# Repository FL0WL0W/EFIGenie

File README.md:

# EFIGenie

An open source engine management. It uses a taskmanager and is coded in a
operation oriented architecture.

The target microcontroller at the moment are the cheap but powerful STM32 line of processors
but any microcontroller can be ported by creating just 4 services,
AnalogService, DigitalService, PwmService, TimerService that can be found in the https://github.com/FL0WL0W/EmbeddedIOServices 
repository. A large benefit to this architecture is that new sensors/abilities/features/etc. 
can be added very easily and can be chosen between the old and new through the configs. 
which means decoders can be changed, sensors added or removed, features added or removed. 
all without having to recompile. There are also some wrapper classes where things like 
two step rev limiters can be implemented or tri-step or even quad-step. still have a list of
things to complete but i am at a state where i am testing the ecu. At this point it has run an engine https://www.youtube.com/watch?v=jJOaTFBkKEE

## Features
* Customizable(size, limits, and axis) 3D Fuel and Ignition Maps (Speed Density, Alpha N)
* Customizable formulas for all engine parameters
* Cusotmizable inputs and outputs
* Unlimited cylinder sequential injection and ignition (Depends on hardware)
  * Stm32Devboard - 8 cylinder sequential fuel and ignition (10, 12, 14, 16 wasted spark/banked injection)
* Flexible Crank Cam Decoder
  * GM 24x (Cam + Crank, Crank Only, or Cam only)
  * Universal 1X decoder
  * Configurable Missing Tooth Decoder
  * --More to come
* Firmware features
  * Unit Tests to ensure everything works
  * Operation Architecture
  * Easily add new sensors

## Diagnostic data handlers

`CommunicationHandler_OBD2PIDRequester` and `CommunicationHandler_OBD2PIDResponder`
use Service `0x01`/`0x41` and 8-bit PIDs. UDS Service `0x22`/`0x62` uses the separate
`CommunicationHandler_UDSDIDRequester` and `CommunicationHandler_UDSDIDResponder`
with 16-bit DIDs. Move existing 16-bit `RegisterPID`/`RequestPID` calls to
`RegisterDID`/`RequestDID`; the service is no longer selected by identifier size.

To expose a PID responder through a DID range:

```cpp
EFIGenie::CommunicationHandler_OBD2PIDResponder pids(communicationService);
EFIGenie::CommunicationHandler_UDSDIDResponder dids(communicationService);
pids.RegisterPID(0x0c, rpmOperation);
dids.RegisterOBD2PIDMirror(0xf4, &pids);
```

A request `22 F4 0C` calls the PID responder locally with `01 0C`, captures its
`41 0C <payload>` response, and returns `62 F4 0C <payload>`. No OBD request is
sent on the bus. The high byte is configurable; supported-PID bitmap requests
are mirrored too, and later PID registrations/unregistrations are reflected
immediately. Explicit `RegisterDID` entries override mirrored entries. Use
`UnregisterOBD2PIDMirror(highByte)` to remove a mirror. Operations and mirrored
responders are borrowed and must outlive their registrations.

The DID responder accepts framed requests containing one or more DIDs, returning
one combined positive response or a negative response if any requested value is
unavailable. Malformed frames return `7F 22 13`; unavailable values return
`7F 22 31`. The DID requester requests and parses one DID per transaction because
multi-DID response payload lengths require application-specific definitions.

## Building
After trying with a few different toolchains the tool chain that seemed to work the best is GCC/G++9.

* Ubuntu 20.04
* GCC/G++9
* CMake

VSCode Extensions:
* C/C++
* CMake
* CMake Tools
* Cortex-Debug
* GoogleTest Adapter

```
sudo apt-get install cmake gcc g++ gdb
```

### Building the Tests
Make 

## TODO List
* *Idle Control
* After Start Enrichment (Add Engine Time Since Started, AE can be configured in GUI with that variable available)
* Customizable(size and seperations) FuelTrim Predictive Multi Channel Historic Table
* Fuel Trim (Wideband/Pid and Narrowband | predictive based on TPS or MAP)
* Transmission Control (Paddle shift transmission solenoid)
* Transmission Control (line pressure control)
* Transmission Control (automatic gear shifts)
* OBD2

> *High Priority

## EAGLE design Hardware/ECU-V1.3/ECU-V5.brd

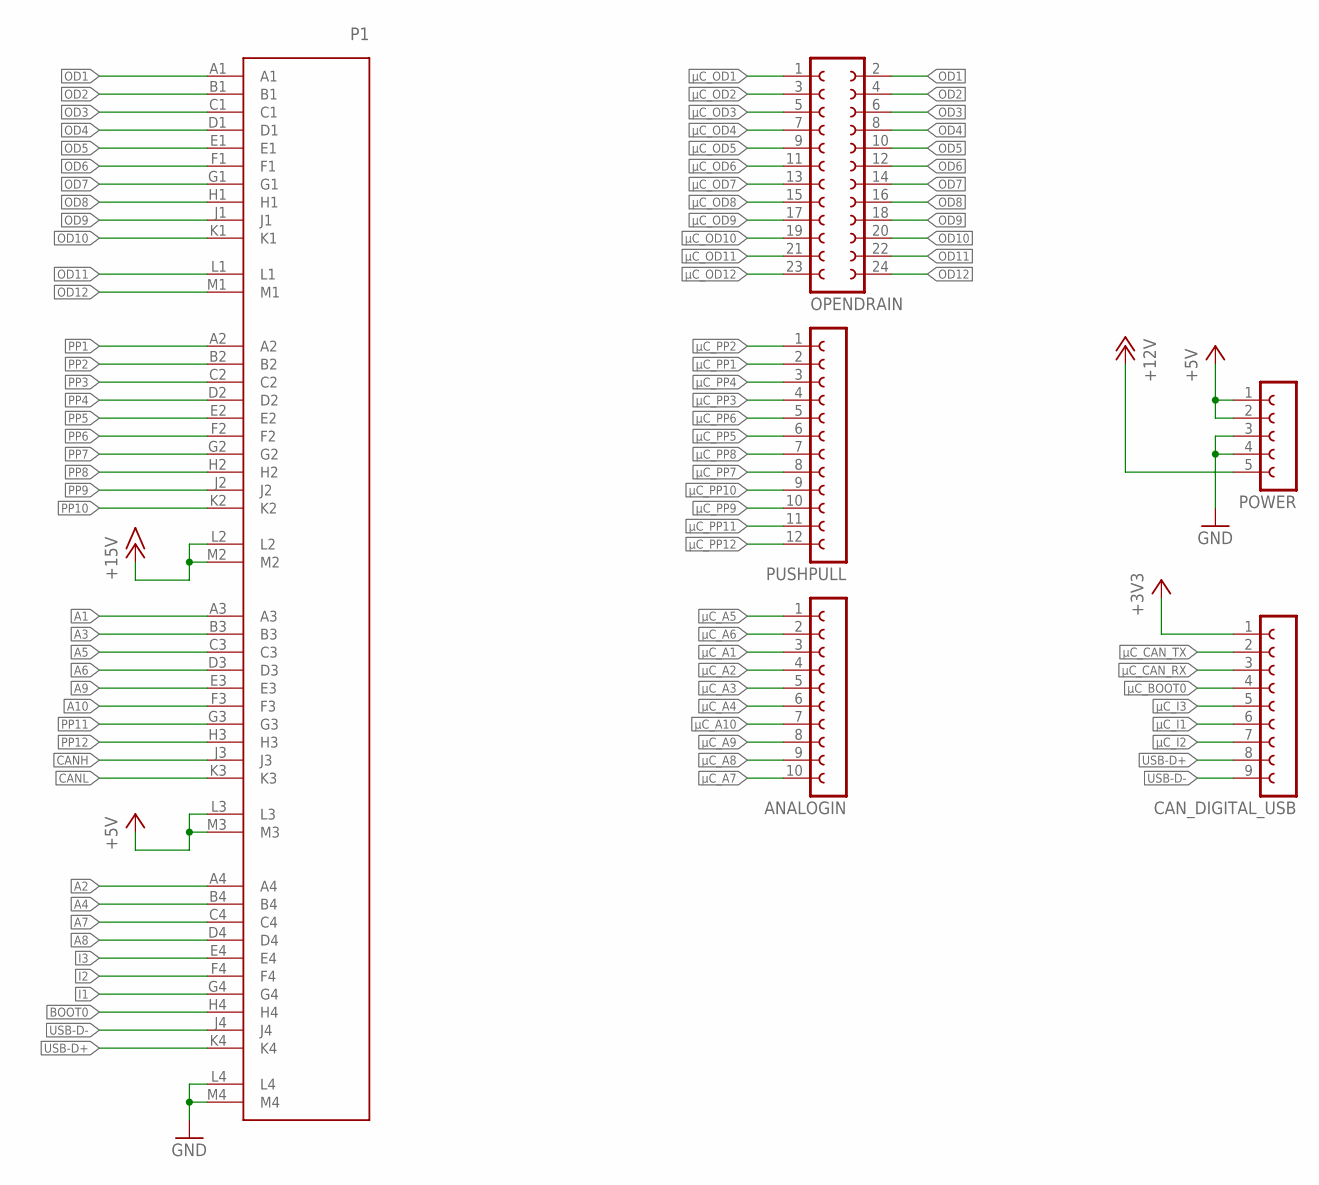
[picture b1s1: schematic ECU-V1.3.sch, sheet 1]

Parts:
ANALOGIN: FE10-1; FE10
CAN_DIGITAL_USB: FE09-1; FE09
OPENDRAIN: FE12-2
P1: ECU-CONNECTOR
POWER: FE05-1
PUSHPULL: FE12-1; FE12

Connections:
+3V3: CAN_DIGITAL_USB.1; also elsewhere on the board
+5V: P1.L3, P1.M3, POWER.1, POWER.2; also elsewhere on the board
+12V: POWER.5; also elsewhere on the board
+15V: P1.L2, P1.M2; also elsewhere on the board
A1: P1.A3; also elsewhere on the board
A2: P1.A4; also elsewhere on the board
A3: P1.B3; also elsewhere on the board
A4: P1.B4; also elsewhere on the board
A5: P1.C3; also elsewhere on the board
A6: P1.D3; also elsewhere on the board
A7: P1.C4; also elsewhere on the board
A8: P1.D4; also elsewhere on the board
A9: P1.E3; also elsewhere on the board
A10: P1.F3; also elsewhere on the board
BOOT0: P1.H4; also elsewhere on the board
CANH: P1.J3; also elsewhere on the board
CANL: P1.K3; also elsewhere on the board
GND: P1.L4, P1.M4, POWER.3, POWER.4; also elsewhere on the board
I1: P1.G4; also elsewhere on the board
I2: P1.F4; also elsewhere on the board
I3: P1.E4; also elsewhere on the board
OD1: OPENDRAIN.2, P1.A1; also elsewhere on the board
OD2: OPENDRAIN.4, P1.B1; also elsewhere on the board
OD3: OPENDRAIN.6, P1.C1; also elsewhere on the board
OD4: OPENDRAIN.8, P1.D1; also elsewhere on the board
OD5: OPENDRAIN.10, P1.E1; also elsewhere on the board
OD6: OPENDRAIN.12, P1.F1; also elsewhere on the board
OD7: OPENDRAIN.14, P1.G1; also elsewhere on the board
OD8: OPENDRAIN.16, P1.H1; also elsewhere on the board
OD9: OPENDRAIN.18, P1.J1; also elsewhere on the board
OD10: OPENDRAIN.20, P1.K1; also elsewhere on the board
OD11: OPENDRAIN.22, P1.L1; also elsewhere on the board
OD12: OPENDRAIN.24, P1.M1; also elsewhere on the board
PP1: P1.A2; also elsewhere on the board
PP2: P1.B2; also elsewhere on the board
PP3: P1.C2; also elsewhere on the board
PP4: P1.D2; also elsewhere on the board
PP5: P1.E2; also elsewhere on the board
PP6: P1.F2; also elsewhere on the board
PP7: P1.G2; also elsewhere on the board
PP8: P1.H2; also elsewhere on the board
PP9: P1.J2; also elsewhere on the board
PP10: P1.K2; also elsewhere on the board
PP11: P1.G3; also elsewhere on the board
PP12: P1.H3; also elsewhere on the board
USB-D+: CAN_DIGITAL_USB.8, P1.K4
USB-D-: CAN_DIGITAL_USB.9, P1.J4
µC_A1: ANALOGIN.3; also elsewhere on the board
µC_A2: ANALOGIN.4; also elsewhere on the board
µC_A3: ANALOGIN.5; also elsewhere on the board
µC_A4: ANALOGIN.6; also elsewhere on the board
µC_A5: ANALOGIN.1; also elsewhere on the board
µC_A6: ANALOGIN.2; also elsewhere on the board
µC_A7: ANALOGIN.10; also elsewhere on the board
µC_A8: ANALOGIN.9; also elsewhere on the board
µC_A9: ANALOGIN.8; also elsewhere on the board
µC_A10: ANALOGIN.7; also elsewhere on the board
µC_BOOT0: CAN_DIGITAL_USB.4; also elsewhere on the board
µC_CAN_RX: CAN_DIGITAL_USB.3; also elsewhere on the board
µC_CAN_TX: CAN_DIGITAL_USB.2; also elsewhere on the board
µC_I1: CAN_DIGITAL_USB.6; also elsewhere on the board
µC_I2: CAN_DIGITAL_USB.7; also elsewhere on the board
µC_I3: CAN_DIGITAL_USB.5; also elsewhere on the board
µC_OD1: OPENDRAIN.1; also elsewhere on the board
µC_OD2: OPENDRAIN.3; also elsewhere on the board
µC_OD3: OPENDRAIN.5; also elsewhere on the board
µC_OD4: OPENDRAIN.7; also elsewhere on the board
µC_OD5: OPENDRAIN.9; also elsewhere on the board
µC_OD6: OPENDRAIN.11; also elsewhere on the board
µC_OD7: OPENDRAIN.13; also elsewhere on the board
µC_OD8: OPENDRAIN.15; also elsewhere on the board
µC_OD9: OPENDRAIN.17; also elsewhere on the board
µC_OD10: OPENDRAIN.19; also elsewhere on the board
µC_OD11: OPENDRAIN.21; also elsewhere on the board
µC_OD12: OPENDRAIN.23; also elsewhere on the board
µC_PP1: PUSHPULL.2; also elsewhere on the board
µC_PP2: PUSHPULL.1; also elsewhere on the board
µC_PP3: PUSHPULL.4; also elsewhere on the board
µC_PP4: PUSHPULL.3; also elsewhere on the board
µC_PP5: PUSHPULL.6; also elsewhere on the board
µC_PP6: PUSHPULL.5; also elsewhere on the board
µC_PP7: PUSHPULL.8; also elsewhere on the board
µC_PP8: PUSHPULL.7; also elsewhere on the board
µC_PP9: PUSHPULL.10; also elsewhere on the board
µC_PP10: PUSHPULL.9; also elsewhere on the board
µC_PP11: PUSHPULL.11; also elsewhere on the board
µC_PP12: PUSHPULL.12; also elsewhere on the board

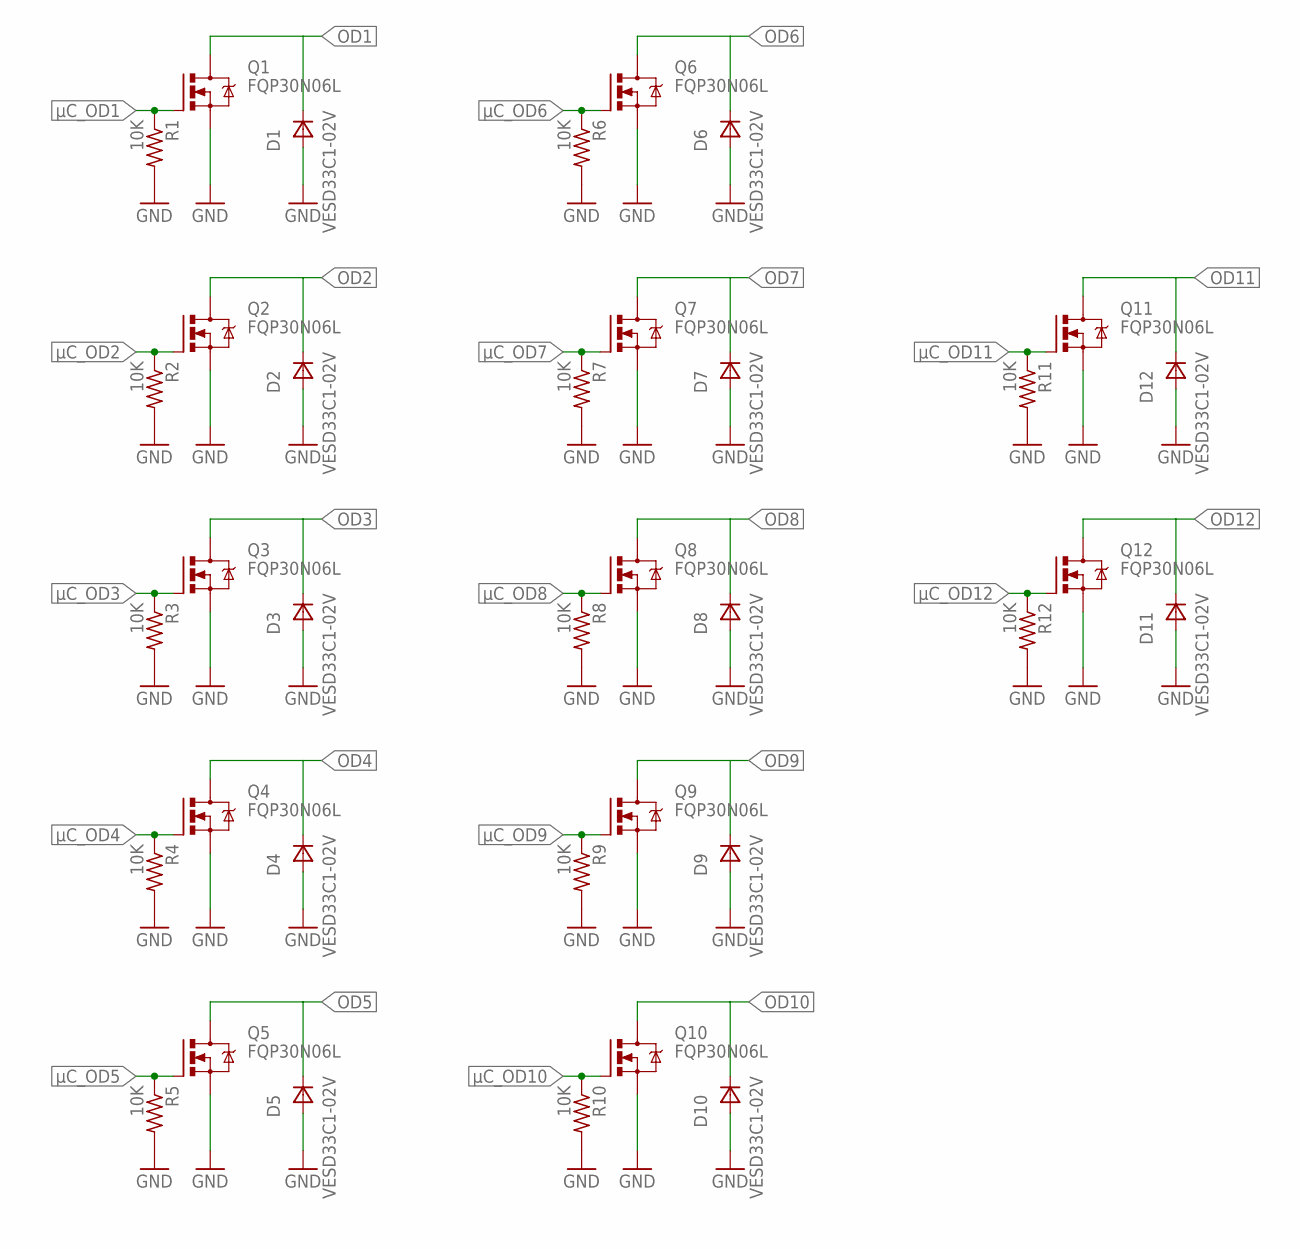
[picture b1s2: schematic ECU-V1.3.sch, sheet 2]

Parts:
D1, D2, D3, D4, D5, D6, D7, D8, D9, D10, D11, D12: VESD33C1-02V; SOD323
Q1, Q2, Q3, Q4, Q5, Q6, Q7, Q8, Q9, Q10, Q11, Q12: FQP30N06L; TO220BV
R1, R2, R3, R4, R5, R6, R7, R8, R9, R10, R11, R12: 10K; R0805

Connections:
GND: D1.2 (A), D2.2 (A), D3.2 (A), D4.2 (A), D5.2 (A), D6.2 (A), D7.2 (A), D8.2 (A), D9.2 (A), D10.2 (A), D11.2 (A), D12.2 (A), Q1.S, Q2.S, Q3.S, Q4.S, Q5.S, Q6.S, Q7.S, Q8.S, Q9.S, Q10.S, Q11.S, Q12.S, R1.2, R2.2, R3.2, R4.2, R5.2, R6.2, R7.2, R8.2, R9.2, R10.2, R11.2, R12.2; also elsewhere on the board
OD1: D1.1 (C), Q1.D; also elsewhere on the board
OD2: D2.1 (C), Q2.D; also elsewhere on the board
OD3: D3.1 (C), Q3.D; also elsewhere on the board
OD4: D4.1 (C), Q4.D; also elsewhere on the board
OD5: D5.1 (C), Q5.D; also elsewhere on the board
OD6: D6.1 (C), Q6.D; also elsewhere on the board
OD7: D7.1 (C), Q7.D; also elsewhere on the board
OD8: D8.1 (C), Q8.D; also elsewhere on the board
OD9: D9.1 (C), Q9.D; also elsewhere on the board
OD10: D10.1 (C), Q10.D; also elsewhere on the board
OD11: D12.1 (C), Q11.D; also elsewhere on the board
OD12: D11.1 (C), Q12.D; also elsewhere on the board
µC_OD1: Q1.G, R1.1; also elsewhere on the board
µC_OD2: Q2.G, R2.1; also elsewhere on the board
µC_OD3: Q3.G, R3.1; also elsewhere on the board
µC_OD4: Q4.G, R4.1; also elsewhere on the board
µC_OD5: Q5.G, R5.1; also elsewhere on the board
µC_OD6: Q6.G, R6.1; also elsewhere on the board
µC_OD7: Q7.G, R7.1; also elsewhere on the board
µC_OD8: Q8.G, R8.1; also elsewhere on the board
µC_OD9: Q9.G, R9.1; also elsewhere on the board
µC_OD10: Q10.G, R10.1; also elsewhere on the board
µC_OD11: Q11.G, R11.1; also elsewhere on the board
µC_OD12: Q12.G, R12.1; also elsewhere on the board

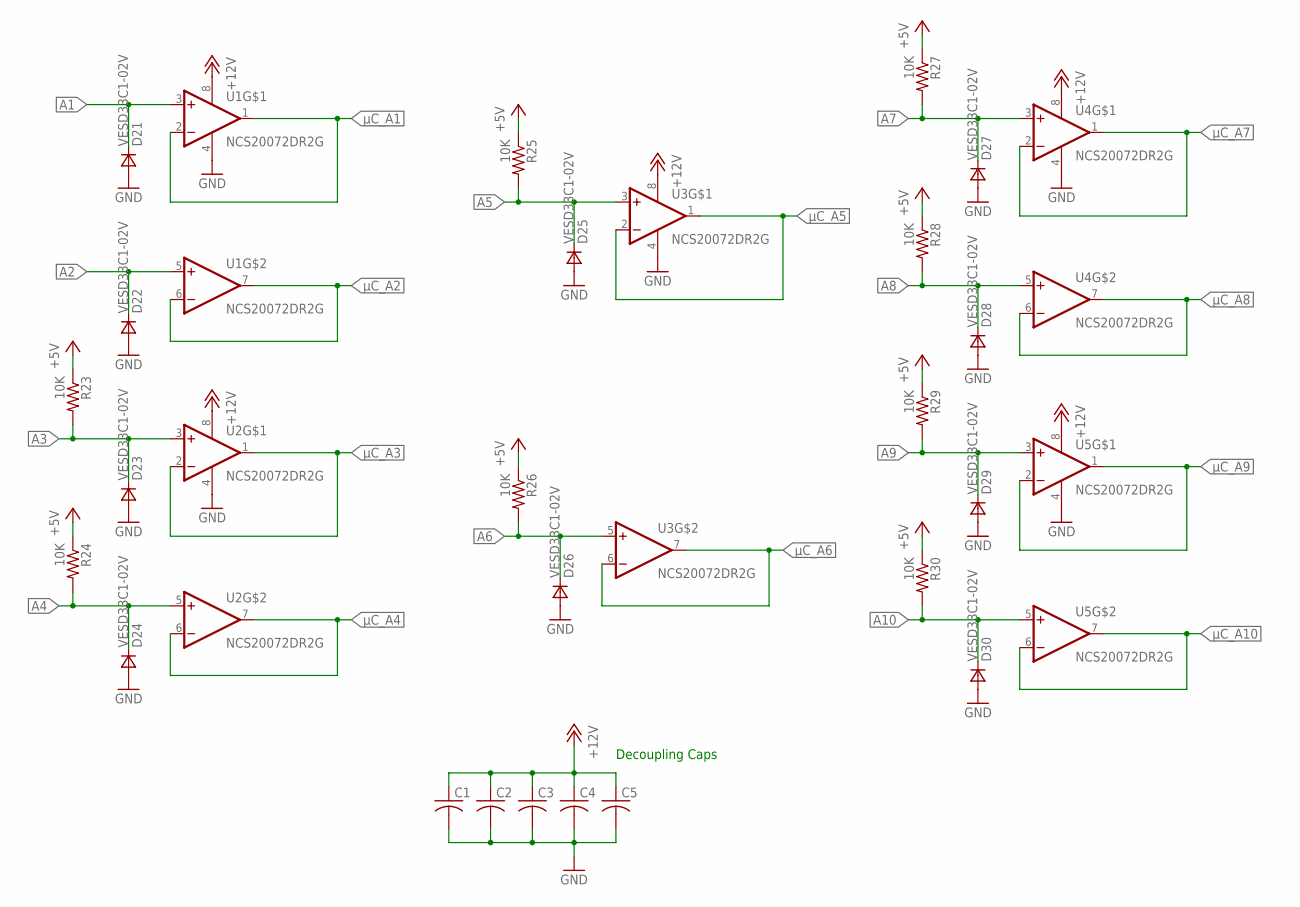
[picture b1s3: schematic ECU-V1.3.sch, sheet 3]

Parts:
C1, C2, C3, C4, C5: C-USC0805; C0805
D21, D22, D23, D24, D25, D26, D27, D28, D29, D30: VESD33C1-02V; SOD323
R23, R24, R25, R26, R27, R28, R29, R30: 10K; R0805
U1, U2, U3, U4, U5: NCS20072DR2G; SOIC8

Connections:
+5V: R23.1, R24.1, R25.1, R26.1, R27.1, R28.1, R29.1, R30.1; also elsewhere on the board
+12V: C1.1, C2.1, C3.1, C4.1, C5.1, U1.8 (V+), U2.8 (V+), U3.8 (V+), U4.8 (V+), U5.8 (V+); also elsewhere on the board
A1: D21.1 (C), U1.3 (+IN); also elsewhere on the board
A2: D22.1 (C), U1.5 (+IN); also elsewhere on the board
A3: D23.1 (C), R23.2, U2.3 (+IN); also elsewhere on the board
A4: D24.1 (C), R24.2, U2.5 (+IN); also elsewhere on the board
A5: D25.1 (C), R25.2, U3.3 (+IN); also elsewhere on the board
A6: D26.1 (C), R26.2, U3.5 (+IN); also elsewhere on the board
A7: D27.1 (C), R27.2, U4.3 (+IN); also elsewhere on the board
A8: D28.1 (C), R28.2, U4.5 (+IN); also elsewhere on the board
A9: D29.1 (C), R29.2, U5.3 (+IN); also elsewhere on the board
A10: D30.1 (C), R30.2, U5.5 (+IN); also elsewhere on the board
GND: C1.2, C2.2, C3.2, C4.2, C5.2, D21.2 (A), D22.2 (A), D23.2 (A), D24.2 (A), D25.2 (A), D26.2 (A), D27.2 (A), D28.2 (A), D29.2 (A), D30.2 (A), U1.4 (V-), U2.4 (V-), U3.4 (V-), U4.4 (V-), U5.4 (V-); also elsewhere on the board
µC_A1: U1.1 (OUT), U1.2 (-IN); also elsewhere on the board
µC_A2: U1.6 (-IN), U1.7 (OUT); also elsewhere on the board
µC_A3: U2.1 (OUT), U2.2 (-IN); also elsewhere on the board
µC_A4: U2.6 (-IN), U2.7 (OUT); also elsewhere on the board
µC_A5: U3.1 (OUT), U3.2 (-IN); also elsewhere on the board
µC_A6: U3.6 (-IN), U3.7 (OUT); also elsewhere on the board
µC_A7: U4.1 (OUT), U4.2 (-IN); also elsewhere on the board
µC_A8: U4.6 (-IN), U4.7 (OUT); also elsewhere on the board
µC_A9: U5.1 (OUT), U5.2 (-IN); also elsewhere on the board
µC_A10: U5.6 (-IN), U5.7 (OUT); also elsewhere on the board

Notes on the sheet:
Decoupling Caps

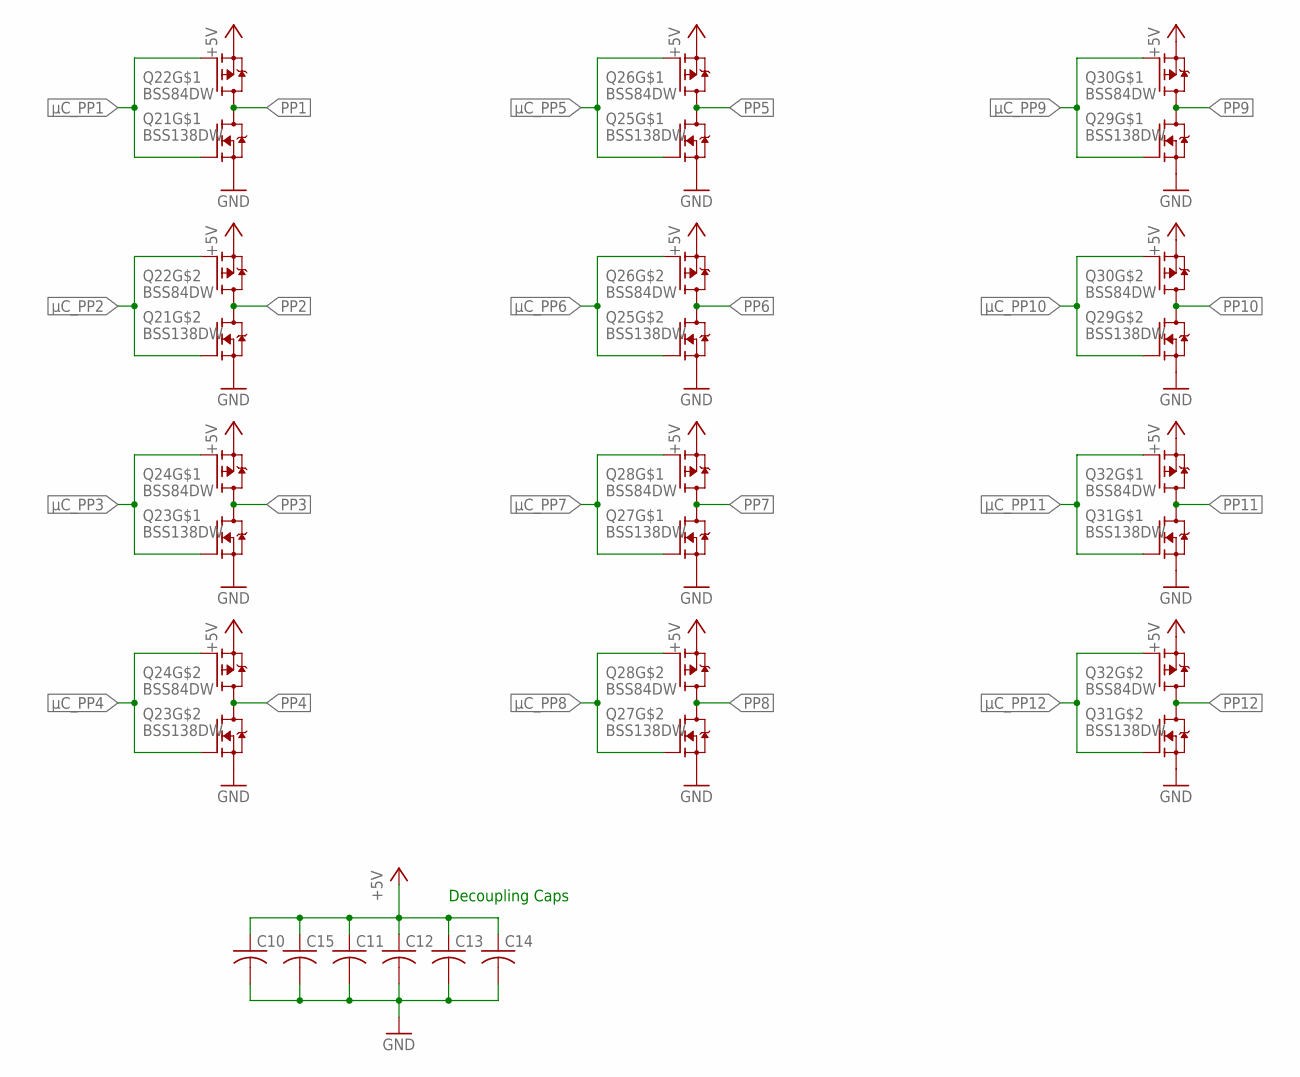
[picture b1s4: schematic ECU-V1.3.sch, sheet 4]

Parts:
C10, C11, C12, C13, C14, C15: C-USC0805; C0805
Q21, Q23, Q25, Q27, Q29, Q31: BSS138DW; SOT363_INFINEON
Q22, Q24, Q26, Q28, Q30, Q32: BSS84DW; SOT363_INFINEON

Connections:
+5V: C10.1, C11.1, C12.1, C13.1, C14.1, C15.1, Q22.1 (S), Q22.4 (S), Q24.1 (S), Q24.4 (S), Q26.1 (S), Q26.4 (S), Q28.1 (S), Q28.4 (S), Q30.1 (S), Q30.4 (S), Q32.1 (S), Q32.4 (S); also elsewhere on the board
GND: C10.2, C11.2, C12.2, C13.2, C14.2, C15.2, Q21.1 (S), Q21.4 (S), Q23.1 (S), Q23.4 (S), Q25.1 (S), Q25.4 (S), Q27.1 (S), Q27.4 (S), Q29.1 (S), Q29.4 (S), Q31.1 (S), Q31.4 (S); also elsewhere on the board
PP1: Q21.3 (D), Q22.3 (D); also elsewhere on the board
PP2: Q21.6 (D), Q22.6 (D); also elsewhere on the board
PP3: Q23.3 (D), Q24.3 (D); also elsewhere on the board
PP4: Q23.6 (D), Q24.6 (D); also elsewhere on the board
PP5: Q25.3 (D), Q26.3 (D); also elsewhere on the board
PP6: Q25.6 (D), Q26.6 (D); also elsewhere on the board
PP7: Q27.3 (D), Q28.3 (D); also elsewhere on the board
PP8: Q27.6 (D), Q28.6 (D); also elsewhere on the board
PP9: Q29.3 (D), Q30.3 (D); also elsewhere on the board
PP10: Q29.6 (D), Q30.6 (D); also elsewhere on the board
PP11: Q31.3 (D), Q32.3 (D); also elsewhere on the board
PP12: Q31.6 (D), Q32.6 (D); also elsewhere on the board
µC_PP1: Q21.5 (G), Q22.5 (G); also elsewhere on the board
µC_PP2: Q21.2 (G), Q22.2 (G); also elsewhere on the board
µC_PP3: Q23.5 (G), Q24.5 (G); also elsewhere on the board
µC_PP4: Q23.2 (G), Q24.2 (G); also elsewhere on the board
µC_PP5: Q25.5 (G), Q26.5 (G); also elsewhere on the board
µC_PP6: Q25.2 (G), Q26.2 (G); also elsewhere on the board
µC_PP7: Q27.5 (G), Q28.5 (G); also elsewhere on the board
µC_PP8: Q27.2 (G), Q28.2 (G); also elsewhere on the board
µC_PP9: Q29.5 (G), Q30.5 (G); also elsewhere on the board
µC_PP10: Q29.2 (G), Q30.2 (G); also elsewhere on the board
µC_PP11: Q31.5 (G), Q32.5 (G); also elsewhere on the board
µC_PP12: Q31.2 (G), Q32.2 (G); also elsewhere on the board

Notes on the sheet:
Decoupling Caps

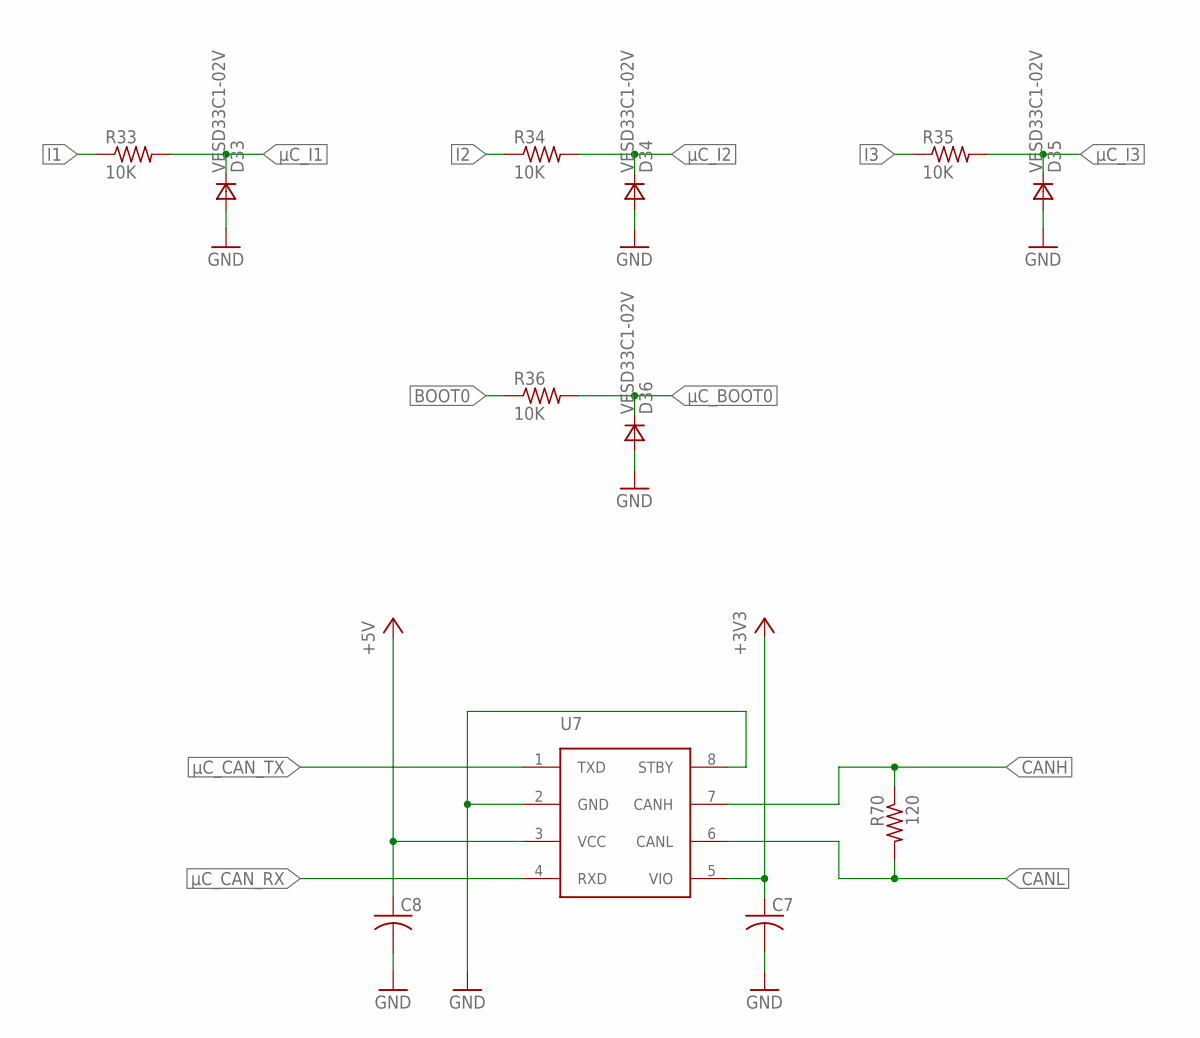
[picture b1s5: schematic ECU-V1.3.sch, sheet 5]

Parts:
C7, C8: C-USC0805; C0805
D33, D34, D35, D36: VESD33C1-02V; SOD323
R33, R34, R35, R36: 10K; R0805
R70: 120; R0805
U7: ATA6561-GA; SO-08

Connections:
+3V3: C7.1, U7.5 (VIO); also elsewhere on the board
+5V: C8.1, U7.3 (VCC); also elsewhere on the board
BOOT0: R36.1; also elsewhere on the board
CANH: R70.1, U7.7 (CANH); also elsewhere on the board
CANL: R70.2, U7.6 (CANL); also elsewhere on the board
GND: C7.2, C8.2, D33.2 (A), D34.2 (A), D35.2 (A), D36.2 (A), U7.2 (GND), U7.8 (STBY); also elsewhere on the board
I1: R33.1; also elsewhere on the board
I2: R34.1; also elsewhere on the board
I3: R35.1; also elsewhere on the board
µC_BOOT0: D36.1 (C), R36.2; also elsewhere on the board
µC_CAN_RX: U7.4 (RXD); also elsewhere on the board
µC_CAN_TX: U7.1 (TXD); also elsewhere on the board
µC_I1: D33.1 (C), R33.2; also elsewhere on the board
µC_I2: D34.1 (C), R34.2; also elsewhere on the board
µC_I3: D35.1 (C), R35.2; also elsewhere on the board

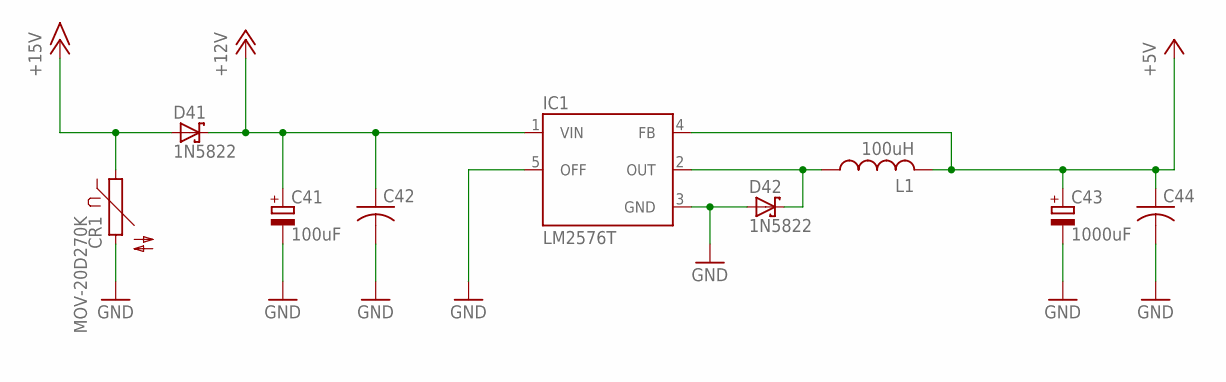
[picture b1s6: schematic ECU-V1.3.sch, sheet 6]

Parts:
C41: 100uF; E3,5-10
C42, C44: C-USC0805; C0805
C43: 1000uF; E3,5-10
CR1: MOV-20D270K; S14K40
D41, D42: 1N5822; DIODE_DO35-7
IC1: LM2576T; TO220-5
L1: 100uH; 6000-XXXX-RC

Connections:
+5V: C43.+, C44.1, IC1.4 (FB), L1.2; also elsewhere on the board
+12V: C41.+, C42.1, D41.C (A), IC1.1 (VIN); also elsewhere on the board
+15V: CR1.1, D41.A (C); also elsewhere on the board
GND: C41.-, C42.2, C43.-, C44.2, CR1.2, D42.A (C), IC1.3 (GND), IC1.5 (OFF); also elsewhere on the board
unnamed: D42.C (A), IC1.2 (OUT), L1.1

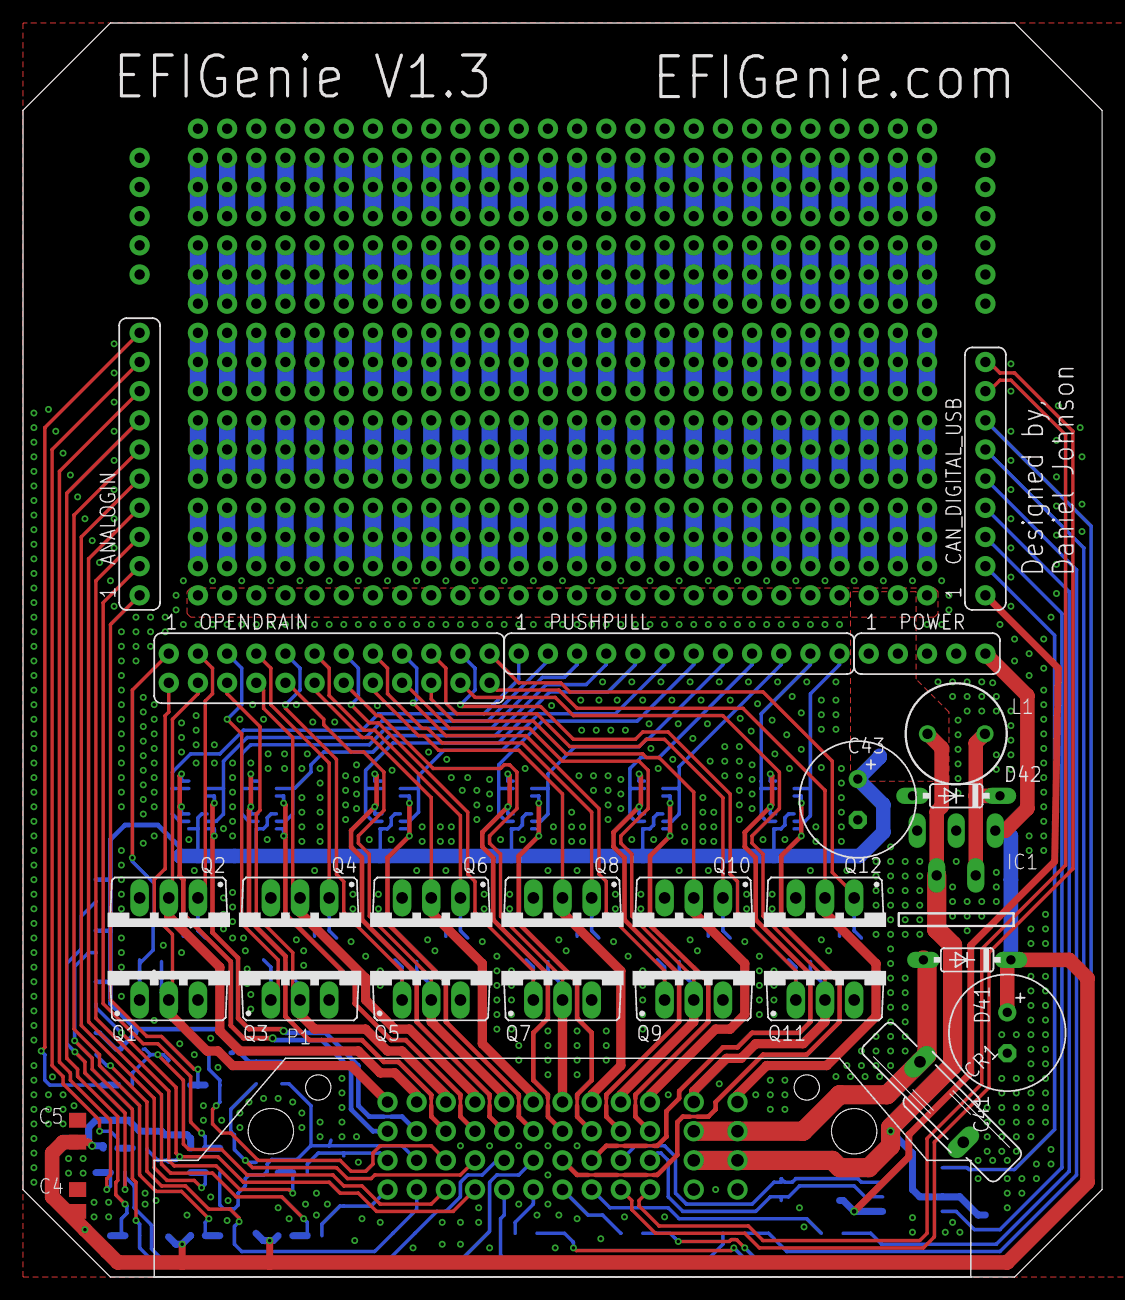
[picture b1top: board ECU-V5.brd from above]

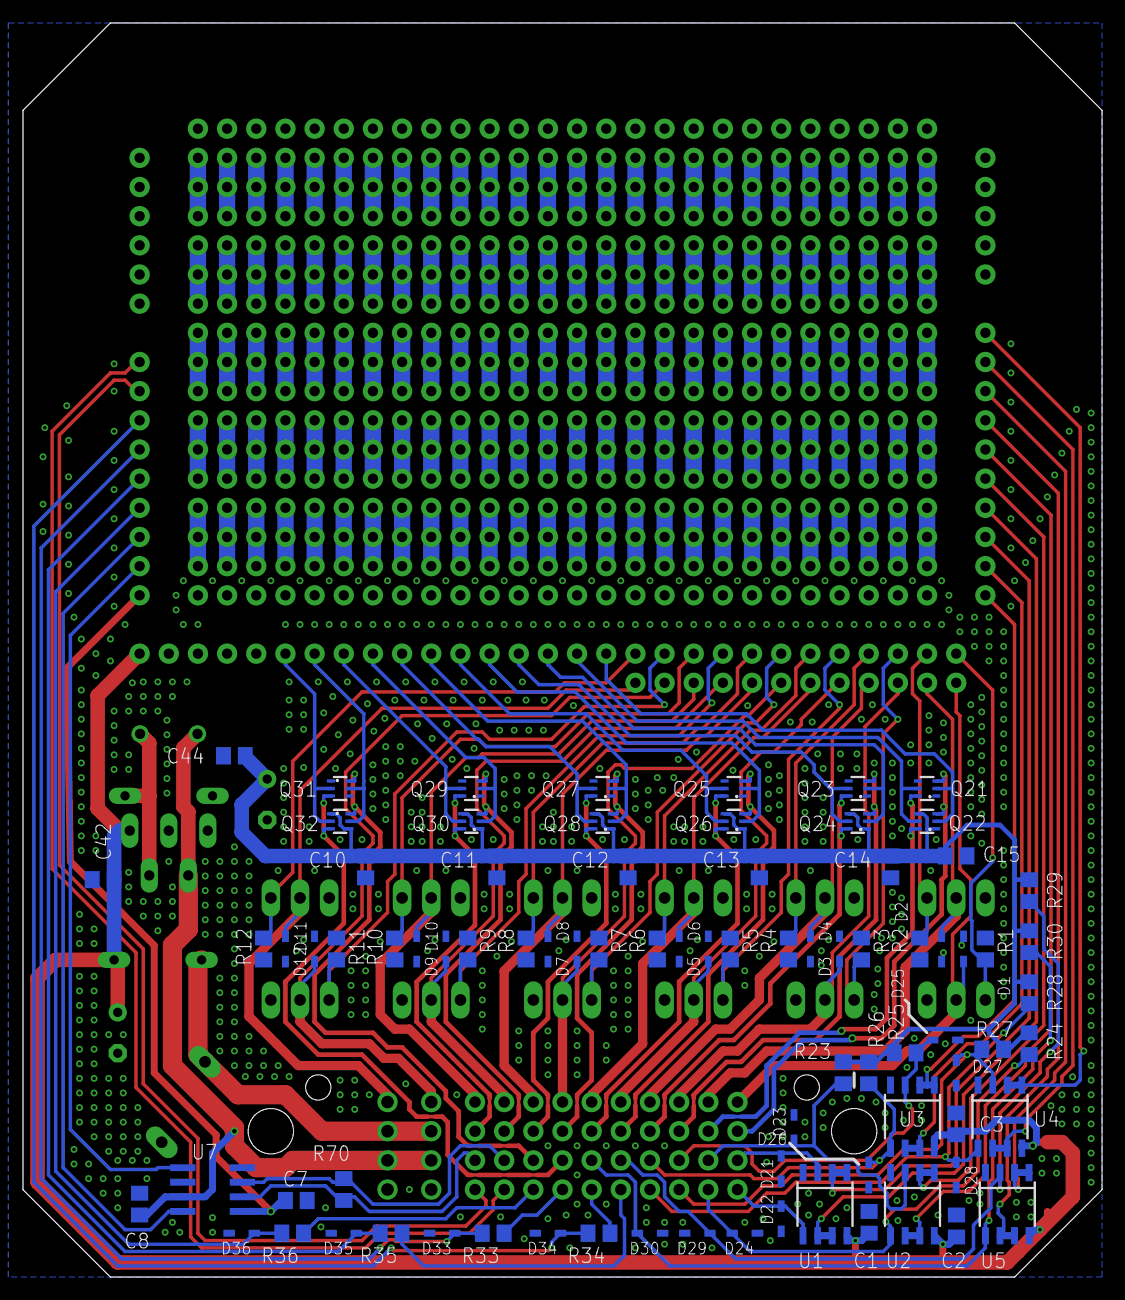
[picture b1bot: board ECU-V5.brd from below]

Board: 2 copper layers, 94.0 x 109.2 mm, 109 parts (82 on the bottom side), 88 nets.

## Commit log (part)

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2022-02-23 flip inputs
2022-02-23 add live voltage to inputs and simplify reluctors
2022-02-24 Group Config Selection
2022-02-24 styling
2022-02-24 More Styling
2022-02-24 refactor naming
2022-02-24 temperature sensor template
2022-02-24 start of Calculation_Operation
2022-02-25 big refactor user getter/setter and Seperation of Concerns between Value and SaveValue
2022-02-25 update libs
2022-02-25 update JS Table
2022-02-25 Min Max and Step need to be converted to display value
2022-02-25 more refactor
2022-02-25 fix table parameter selection
2022-02-25 propogate input name all the way to translation table
2022-02-25 more variable bubbling
2022-02-25 remove input whenever measurement is change and no match
2022-02-25 fix input control buttons
2022-02-25 more work on Calculation_Operation
2022-02-28 stylize and performance
2022-02-28 Show realtime values as gauges #5
2022-02-28 undue test code
2022-02-28 Selectable Units #17
2022-02-28 save unit selection by name instead of index
2022-02-28 stylizing
2022-02-28 scale mobile correctly
2022-02-28 scale input overlay
2022-02-28 fix context menu location
2022-02-28 single unit measurements don't need context menu
2022-03-02 update javascript table
2022-03-02 update jstable
2022-03-03 Configurable Axis for Table Interpolation
2022-03-03 updagte js table
2022-03-08 bug fixes with pin overlay
2022-03-08 minor styling
2022-03-08 calculation able to select none
2022-03-08 Group operation
2022-03-08 group consolidation
2022-03-08 cleanup
2022-03-08 pinselect supported modes
2022-03-08 add dropdown caret
2022-03-08 remove label for selections
2022-03-08 refactor
2022-03-09 big refactor in progress
2022-03-09 UISelection Refactor
2022-03-09 UISelection refactor fixes
2022-03-09 Rename UI. to UI.Old
2022-03-10 UITemplate
2022-03-10 Initial Table Refactor
2022-03-12 rafactor into extending ui elements
2022-03-12 table styling
2022-03-12 more UITable implementation
2022-03-12 some more UITable Implementation
2022-03-12 Table paste
2022-03-12 resolution drag
2022-03-12 more table implementation
2022-03-12 UITable selecting
2022-03-13 selecting bug fix
2022-03-13 modify bug fixes
2022-03-13 add value to template
2022-03-13 integrate new table
2022-03-13 styling and table replacement
2022-03-13 integration and table trail
2022-03-14 rearrange table and add move graph into its own element so table is not 2000 lines long
2022-03-14 move statics next to constructor
2022-03-14 remove unused event parameters
2022-03-14 UIGraph3D
2022-03-14 graph scale value with min/max
2022-03-14 add interpolation when changing resolution
2022-03-14 bug fix
2022-03-14 fix depth and scale heights to the height/width ratio
2022-03-15 bug fixes and zoom
2022-03-15 simplify table selecting and implement UIGraph event listeners
2022-03-15 implement dragvalue
2022-03-15 deobfuscate move and rotate
2022-03-15 optimizations
2022-03-17 UIGraph3D Axis
2022-03-17 axis value labels
2022-03-17 update axis when changed
2022-03-17 attach tables together
2022-03-17 fixes
2022-03-17 optimization
2022-03-18 z axis
2022-03-18 attach table in UI index
2022-03-18 implement UIMeasurement
2022-03-18 NumberWithMeasurement
2022-03-24 copy paste fixes
2022-03-24 simplify interpolatexy
2022-03-24 UIGraph2D template
2022-03-24 more 2d graph implementation
2022-03-24 more copy fixes
2022-03-26 UIGraph2D implementation
2022-03-26 2D graph implementation finished
2022-03-26 bug fixes
2022-03-27 move UI to repo
2022-03-27 convert to JavascriptUI repo
2022-03-27 more migration
2022-03-27 update to new dialog
2022-03-27 update JSUI
2022-03-28 all configs refactored. top level configs next
2022-03-28 remove comment
2022-03-28 convert input to new template
2022-03-28 onChange removal
2022-03-28 remove onchange
2022-03-29 more template conversions
2022-03-30 ConfigInputs conversion to UI.Template
2022-03-30 remove unneeded ui icons
2022-03-30 remove jquery ui css
2022-04-01 more inputs implementation
2022-04-01 remove jquery from overlay
2022-04-01 remove jquery from everything except ajax :(
2022-04-01 fix overlay
2022-04-02 jquery gone
2022-04-03 start of formula implementation
2022-04-03 Formula Prototype
2022-04-04 more formula implementation, performance optimizations, and styling
2022-04-04 more formula implementation
2022-04-05 formula fully implemented
2022-04-05 Set up build tools with Vite
2022-04-06 convert to modules
2022-04-06 more modules
2022-04-06 variable naming refactor
2022-04-06 measurement variable name refactor
2022-04-06 more variable name refactoring
2022-04-06 more variable naming refactor
2022-04-06 inputs variable name refactor
2022-04-06 resize graph on table resize
2022-04-06 Everything is a module now
2022-04-12 register operations
2022-04-12 boolean formula
2022-05-14 minor fixes. added hook for custom CalculationOrVariableFilter
2022-05-14 small fixes and styling
2022-06-01 Update Get Variable Handler
2022-06-02 update googletest
2022-06-02 better communication service abstraction
2022-06-05 pass in variable map to EFIGenieMain and make schedule deletion safe
2022-06-05 add crc
2022-06-05 fix instances
2022-06-05 fix tests
2022-06-05 Instance and GUI fixes
2022-06-07 update EmbeddedIOServices
2022-06-08 Fix Reluctor_Universal1x config
2022-06-08 fix variable registry
2022-06-08 configSize fix
2022-06-12 GUI Fixes
2022-06-12 update serial protocol
2022-06-12 limit zeros to add
2022-06-12 make enable work the same as sync
2022-06-12 update ReluctorOperations
2022-06-12 burn binary from browser and server html from python #26
2022-06-19 selection reference instead of object
2022-06-19 Start decoupling gui from binary creation
2022-06-19 more decoupling of gui from binary
2022-06-27 remove referenceName and outputVariableId
2022-06-28 consolidate all groups
2022-06-28 more binary decoupling
2022-06-29 more decoupling binary
2022-06-29 decouple binary from gui
2022-06-29 refactoring
2022-06-30 add hardware
2022-07-01 more decoupling
2022-07-01 decouple top
2022-07-02 output fixes
2022-07-02 close sidebar when on touch devices
2022-07-06 ground work for measurement formula
2022-07-07 remove semicolons and other refactor
2022-07-07 cleanup and remember last tab
2022-07-07 displayUnits
2022-07-07 formula with units
2022-07-07 when no units specified. assume either boolean or ratio and filter accordingly
2022-07-07 small fix
2022-07-07 remember sidebar expansion
2022-07-08 small fixes
2022-07-09 update hardware
2022-07-09 fix pdf
2022-07-09 serial and gui fixes
2022-07-09 remove debugger
2022-07-09 another attempt at removing javascripttable module
2022-07-09 js error fix
2022-07-09 bin generation fixes
2022-07-09 default sequential false
2022-07-10 webserial
2022-07-13 webserial fully replace python
2022-07-13 add live server to recommended extenstion
2022-07-13 log into object instead of array
2022-07-13 fix metadata
2022-07-14 make webserial more robust and readable
2022-07-14 recfactor and robustness
2022-07-14 simple refactor
2022-07-16 fix variable creation
2022-07-16 selectable edges for Universal 1X reluctor
2022-07-16 fix GetVariableId
2022-07-16 Universal1X selectable edges
2022-07-16 Log at 100Hz, display live values at 10Hz
2022-07-16 better destructor for schedule
2022-07-16 fix registervariables on change
2022-07-18 bug fixes and Ignition Schedule correctly transition between Sequential and Not Seqeuntial
2022-07-21 GetVariableId fix
2022-07-21 fix for saving compressed
2022-08-25 Alpha N
2022-08-25 add unit configuration to cusom inputs
2022-08-26 config generation fixes
2022-09-01 update JavascriptUI
2022-09-01 Configurable number of outputs
2022-09-19 Linear TPS
2022-09-20 TPS Calibration
2022-09-21 calibration fixes
2022-10-30 TPS calibrate opposite polarity
2022-10-30 no variables inside input selection
2022-11-01 selectable units for generic calculations. selectable units for table
2022-11-02 add measurement label to custom input
2022-11-02 axis units
2022-11-02 unit is secondary selection instead of included in parameter
2022-11-03 2AxisTable Unit as secondary selection
2022-11-03 loading optimizations
2022-11-03 fixes. UITableWithUnit has unit issue
2022-11-03 fix uitablewithunit loading
2022-11-04 table formula and parameter fixes
2022-11-04 variable selection on measurement
2022-11-07 bin fixes
2022-11-07 fixes and tps calibration fix
2022-11-07 add comments on parameter parsing
2022-11-07 add not operator to formula
2022-11-07 formula fixes and not implementation
2022-11-07 unit conversion for calcorvariable selection
2022-11-07 UIGauge
2022-11-08 Dashboard with gauges
2022-11-08 update google test
2022-11-09 gauge fix
2022-11-15 Configurable Axis for Table Interpolation #2
2022-11-15 update OA
2022-12-01 fix dashboard gauge units when loading
2022-12-22 more Dashboard work
2022-12-28 fix gauge unit display
2022-12-28 maximum 25 ticks for gauge
2022-12-30 Inputs Refactor
2023-01-08 validation for gui
2023-01-08 ability to use self in formula. useful for hysteresis
2023-01-17 Naming Refactor
2023-01-18 Warning fixes
2023-05-29 update googlttest
2023-06-17 ubuntu development environment setup script
2023-10-03 update gtest
2023-10-14 update cmakepresets for debug
2023-12-19 update libs and make editor usable
2024-03-15 EmbeddedIOServices removed ICommunicationHandler
2024-03-17 update embeddediooperations
2024-03-18 remove unneded intermediate size variable
2024-03-18 reconfigure when files added/deleted
2024-03-22 ConfigList gui
2024-03-22 attach outputs to change event
2024-03-22 Injector/Ignition outputs on a single line
2024-03-22 add static configurations to configlist
2024-03-23 generic calculations able to be added anywhere
2024-03-28 binary builder for ConfigList
2024-03-29 CAN GUI
2024-04-01 can read binary build
2024-04-01 Revert "remove unneded intermediate size variable"
    This reverts commit b0bcdd62ec67c710ab18f0c1fa58ef5476616c15.
2024-04-01 fix acceptance test
2024-04-01 CAN write binary build
2024-04-02 CommunicationHandler_EFIGenie
2024-04-02 pull metadata out of config
2024-04-03 FetchContent
2024-04-03 link public
2024-04-03 remove submodules
2024-04-03 this to & on macro in communicationhandler
2024-11-20 move editor to its own repo
2024-11-22 add ExpanderMain
2024-11-23 fix lambda variablers being optimized away on ESP32
2024-11-30 moved lib sources to root dir
2024-11-30 move to testmate
2025-01-24 EFIGenie Handler with no config metadata
2025-01-29 Start/Middle/End Injection Angle #36
2025-01-29 weed out eroneous rpm
2025-02-06 initialise closeAt
2026-02-07 update to Unix Makefiles
2026-05-29 add expander acceptance test
2026-06-09 added ignition and injection unit tests as well as fixed 100% duty cycle injectors #39
